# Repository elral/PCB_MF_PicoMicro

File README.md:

# ✈️ PicoMicro - ProMicro-Compatible Board from Mobiflight

This board is designed as a **drop-in replacement** for the classic Arduino Pro Micro (ATmega32U4), but powered by the **modern Raspberry Pi RP2350A microcontroller**.  
It keeps the same **form factor and pinout** while offering massive improvements in performance, memory, and connectivity — making it the **ideal choice for Mobiflight cockpits**.

---

## 🚀 Why PicoMicro for Mobiflight?

### ⚡ Drop-In Upgrade
- Identical footprint & pinout to the Arduino Pro Micro  
- Works with existing wiring and PCB layouts → **no hardware redesign required**  

### 📈 Higher Performance for Complex Cockpits
- **Dual-core ARM Cortex-M33 @ up to 150 MHz** (with FPU & DSP)  
- Handles many encoders, switches, LEDs, and displays simultaneously  
- **512 KB SRAM + up to 16 MB Flash** → no memory limits for complex setups  

### 🔌 Richer Connectivity
- **Native USB 2.0 FS/HS**  

### ⚡ True 5V Compatibility
- **5V-tolerant I/O pins** → safe with legacy 5V sensors, LEDs, and modules  
- Fully compatible with most cockpit electronics  

### 🔋 Efficiency & Reliability
- ARM-based low-power modes for large setups  
- Stable & future-proof, backed by Raspberry Pi Foundation support

---

## ⚠️ Known Limitations vs. Arduino Pro Micro

While this board is highly compatible, there are a few important differences:

1. **Analog Inputs**  
   - Only **A0 to A3** are available (4 total)  
   - Other analog pins present on the Pro Micro are not supported  

2. **5V Output (Pin 21)**  
   - On the Arduino Pro Micro, Pin 21 outputs **5V**  
   - On this board, Pin 21 outputs **3.3V**  

3. **MAX7219 & 5V Requirement**  
   - The MAX7219 driver must still be powered with **5V**  
   - Therefore, an **external 5V source** is required, or you can use **Pin 24 (Vin)**, which provides 5V directly from the USB connector  

4. **Level Shifting for MAX7219**  
   - The MAX7219 requires **5V logic levels**  
   - Use a **level shifter** between the PicoMicro board (3.3V signals) and the MAX7219 inputs  

5. **Bootloader Button**  
   - The board includes a **dedicated BOOT button** to enter USB mass storage boot mode (for firmware flashing).  

---

## 📊 PicoMicro vs. Arduino Pro Micro (ATmega32U4)

| Feature  | PicoMicro ProMicro                          | Arduino Pro Micro (ATmega32U4) |
|----------|-------------------------------------------|--------------------------------|
| MCU      | Dual-core ARM Cortex-M33 @ up to 150 MHz, FPU, DSP | 8-bit AVR @ 16 MHz |
| Flash    | Up to 16 MB QSPI (typ. 2–8 MB onboard)    | 32 KB |
| RAM      | 512 KB                                    | 2.5 KB |
| USB      | Native USB 2.0 FS/HS, multiple device classes | Native USB 2.0 FS (limited) |
| I/O      | **3.3 V logic, 5 V-tolerant pins**        | 5 V I/O (native) |
| Analog   | 4 (A0–A3 only)                            | 12 (depending on variant) |
| Extra HW | 2× PIO, Crypto engine, more UART/SPI/I²C | – |
| Power    | Low-power modes, efficient ARM design     | Limited power saving |

---

## 🔧 Example Wiring (MAX7219 with External 5V)

When using a MAX7219 with this PicoMicro board, note the following:

- The MAX7219 **requires 5V power** for reliable operation.
- The PicoMicro board only provides **3.3V logic**, so a **level shifter** is required on the SPI signals.
- Use the `Vin` pin (Pin 24, USB 5V) as the 5V source if no external supply is available.
- Do **not** use Pin 21 (`5V`), as it only provides 3.3V on this board.

#### Wiring Notes

- **Vin (5V USB)** → **VCC (5V MAX7219)**
- **GND** → **GND**
- **MOSI (3.3V)** → (via level shifter) → **DIN (5V)**
- **SCK (3.3V)** → (via level shifter) → **CLK (5V)**
- **CS (3.3V)** → (via level shifter) → **LOAD/CS (5V)**

Make sure to add a **3.3V → 5V level shifter** on the SPI signals to the MAX7219.

#### Block Diagram

---

## 🖥 Advantages for Mobiflight Community Devices

Many Mobiflight **Custom Devices** (Community Devices) are more complex and require more memory and processing power than the classic Arduino Pro Micro can provide.  
This board with the **RP2350A** offers clear advantages:

- **More Flash** → room for larger device code and libraries.  
- **More RAM** → essential for OLED displays and complex buffers.  
- **Higher performance** → smoother updates and faster response.  
- **Dual-Core CPU** → allows splitting tasks (e.g., handling displays and inputs in parallel).  
- **PIO offload** → precise timing for LEDs, drivers, or custom protocols  

This makes the PicoMicro board especially well-suited for **community-driven Mobiflight devices**, including setups with **OLED displays** and other resource-demanding modules.

---

## ✈️ Why It Matters for Mobiflight
- **Supports more devices per board** → fewer boards, fewer USB connections
- **Fast response times** → smoother input/output handling with no lag
- **Drop-in compatibility** → works in place of the Pro Micro in your cockpit modules  
- **Future-ready** → while the ATmega32U4 reaches its limits, the PicoMicro provides plenty of headroom for upcoming Mobiflight features  

---

## 📌 Summary
The **PicoMicro** is a **next-generation upgrade** built for Mobiflight cockpit builders:  
✅ More performance & memory  
✅ 5V-tolerant IO  
✅ 100% ProMicro form factor  
✅ Ideal for complex community devices, including OLEDs

> **Upgrade your cockpit today — with transparent compatibility notes for a smooth migration.**

## Additional information

### Bottom View

### Schematic

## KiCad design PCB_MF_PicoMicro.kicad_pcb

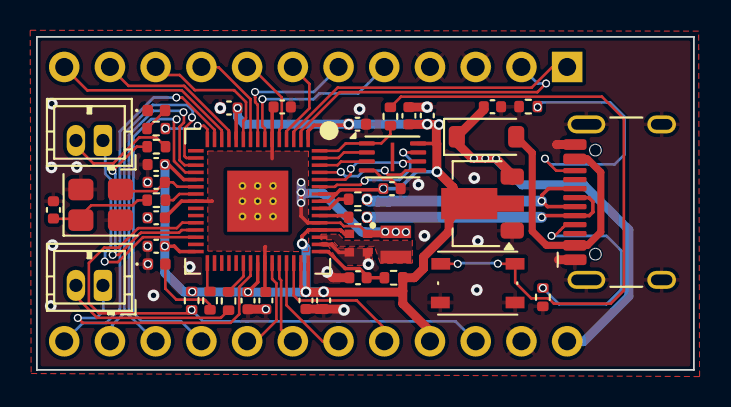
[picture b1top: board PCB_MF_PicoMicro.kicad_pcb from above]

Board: 2 copper layers, 36.5 x 18.5 mm, 44 parts (0 on the bottom side), 52 nets.

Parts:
C1, C2: 10uF; C_0402_1005Metric
C3: 100n; C_0402_1005Metric
C4, C5: 10pF; C_0402_1005Metric
C6, C7, C8, C9, C10, C11, C12, C13, C14, C15: 100nF; C_0402_1005Metric
C16, C17: 4.7u; C_0402_1005Metric_small_pads
C18: 4.7u; C_0402_1005Metric
C19: 4.7uF; C_0402_1005Metric
D1: D_Schottky; D_SOD-123
D2, D3: green; LED_0402_1005Metric
J1: PicoMicro
J3: USB_C_Receptacle_USB2.0_16P; USB_C_Receptacle_HCTL_HC-TYPE-C-16P-01A
J7, J8: Conn_01x02_Pin; JST_ZH_B2B-ZR_1x02_P1.50mm_Vertical
L1: 3.3u; L_pol_2016
R1, R2: 1k; R_0402_1005Metric
R3, R4: 27; R_0402_1005Metric
R5: 33; R_0402_1005Metric
R6: 10k; R_0402_1005Metric
R7, R8: 5.1k; R_0402_1005Metric
R9, R10: 200; R_0402_1005Metric
R11, R12: 50; R_0402_1005Metric
SW1: SW_Push; SW_Push_1P1T_NO_Vertical_Wuerth_434133025816
U1: RP2350A; RP2350A_QFN-60_EP_7.75x7.75_Pitch0.4mm
U2: AMS1117-3.3; SOT-89-3
U4: W25Q16JVSS; Winbond_USON-8-1EP_3x2mm_P0.5mm_EP0.2x1.6mm
Y1: X322512MSB4SI; Crystal_SMD_3225-4Pin_3.2x2.5mm

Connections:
3.3V: C2.1, C3.1, C9.1, C10.1, C11.1, C12.1, C13.1, C14.1, C15.1, C16.1, C19.1, J1.21 (+3.3V), R5.1, R6.1, U1.1 (IOVDD), U1.11 (IOVDD), U1.20 (IOVDD), U1.30 (IOVDD), U1.38 (IOVDD), U1.44 (ADC_AVDD), U1.45 (IOVDD), U1.49 (VREG_VIN), U1.53 (USB_OTP_VDD), U1.54 (QSPI_IOVDD), U2.2 (VO), U4.8 (VCC)
+1V1: C6.1, C7.1, C8.1, C17.1, L1.1, U1.6 (DVDD), U1.23 (DVDD), U1.39 (DVDD), U1.50 (VREG_FB)
/RP2350A/GPIO11: R9.2, U1.15 (GPIO11)
/RP2350A/GPIO19: R10.2, U1.31 (GPIO19)
/RP2350A/QSPI_SCLK: U1.56 (QSPI_SCLK), U4.6 (CLK)
/RP2350A/QSPI_SD0: U1.57 (QSPI_SD0), U4.5 (DI(IO0))
/RP2350A/QSPI_SD1: U1.59 (QSPI_SD1), U4.2 (DO(IO1))
/RP2350A/QSPI_SD2: U1.58 (QSPI_SD2), U4.3 (IO2)
/RP2350A/QSPI_SD3: U1.55 (QSPI_SD3), U4.7 (IO3)
/RP2350A/QSPI_SS: R1.1, U1.60 (QSPI_SS), U4.1 (~CS)
/RP2350A/RAW: D1.2 (A), J3.A4 (VBUS), J3.A9 (VBUS), J3.B4 (VBUS), J3.B9 (VBUS)
/RP2350A/USB_D+: J3.A6 (D+), J3.B6 (D+), R3.1
/RP2350A/USB_D-: J3.A7 (D-), J3.B7 (D-), R4.1
/RP2350A/USB_D_R+: R3.2, U1.52 (USB_DP)
/RP2350A/USB_D_R-: R4.2, U1.51 (USB_DM)
/RP2350A/VREG_LX: L1.2, U1.48 (VREG_LX)
/RP2350A/XIN: C4.1, U1.21 (XIN), Y1.3
/RP2350A/XOUT_R: R2.1, U1.22 (XOUT)
/RP2350A/~USB_BOOT: R1.2, SW1.2
A0: J1.17 (18(A0)), U1.40 (GPIO26_ADC0)
A1: J1.18 (19(A1)), U1.41 (GPIO27_ADC1)
A2: J1.19 (20(A2)), U1.42 (GPIO28_ADC2)
A3: J1.20 (21(A3)), U1.43 (GPIO29_ADC3)
D0: J1.2 (0(PWM)/RX), U1.2 (GPIO0)
D1: J1.1 (1(PWM)/TX), U1.3 (GPIO1)
D2: J1.7 (4(PWM)), U1.4 (GPIO2)
D3: J1.8 (5(PWM)), U1.5 (GPIO3)
D4: J1.5 (2(PWM)/SDA), U1.7 (GPIO4)
D5: J1.6 (3(PWM)/SCL), U1.8 (GPIO5)
D6: J1.9 (6(PWM)), U1.9 (GPIO6)
D7: J1.10 (7(PWM)), U1.10 (GPIO7)
D8: J1.11 (8(PWM)), U1.12 (GPIO8)
D9: J1.12 (9(PWM)), U1.13 (GPIO9)
D10: J1.13 (10(PWM)), U1.14 (GPIO10)
D13: J1.14 (16), U1.17 (GPIO13)
D14: J1.15 (14), U1.18 (GPIO14)
D15: J1.16 (15), U1.19 (GPIO15)
GND: C1.2, C2.2, C3.2, C4.2, C5.2, C6.2, C7.2, C8.2, C9.2, C10.2, C11.2, C12.2, C13.2, C14.2, C15.2, C16.2, C17.2, C18.2, C19.2, D2.1 (K), D3.1 (K), J1.3 (GND), J1.4 (GND), J1.23 (GND), J3.A1 (GND), J3.A12 (GND), J3.B1 (GND), J3.B12 (GND), J3.S1 (SHIELD), R7.1, R8.1, SW1.1, U1.47 (VREG_PGND), U1.61 (GND), U2.1 (GND), U4.4 (GND), Y1.2, Y1.4
unnamed: C5.1, R2.2, Y1.1
unnamed: D2.2 (A), R10.1
unnamed: D3.2 (A), R9.1
unnamed: J3.A5 (CC1), R7.2
unnamed: J3.B5 (CC2), R8.2
unnamed: J7.2, R11.1
unnamed: J8.2, R12.1
unnamed: C18.1, R5.2, U1.46 (VREG_AVDD)
RST: J1.22 (RESET), R6.2, U1.26 (RUN)
RX1: J7.1, U1.28 (GPIO17)
RX2: J8.1, U1.37 (GPIO25)
TX1: R11.2, U1.27 (GPIO16)
TX2: R12.2, U1.36 (GPIO24)
VIN: C1.1, D1.1 (K), J1.24 (VIN), U2.3 (VI)

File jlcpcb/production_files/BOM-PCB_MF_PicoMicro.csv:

Comment,Designator,Footprint,LCSC,Quantity
1k,"R1,R2",R_0402_1005Metric,C11702,2
100nF,"C10,C11,C12,C13,C14,C15,C3,C6,C7,C8,C9",C_0402_1005Metric,C1525,11
10uF,"C1,C2",C_0402_1005Metric,C15525,2
4.7u,"C16,C17,C18,C19",C_0402_1005Metric_small_pads,C23733,4
200,"R10,R9",R_0402_1005Metric,C25087,2
27,"R3,R4",R_0402_1005Metric,C25100,2
33,R5,R_0402_1005Metric,C25105,1
50,"R11,R12",R_0402_1005Metric,C25120,2
10k,R6,R_0402_1005Metric,C25744,1
5.1k,"R7,R8",R_0402_1005Metric,C25905,2
W25Q16JVSS,U4,Winbond_USON-8-1EP_3x2mm_P0.5mm_EP0.2x1.6mm,C2843335,1
Conn_01x02_Pin,"J7,J8",JST_ZH_B2B-ZR_1x02_P1.50mm_Vertical,C2845550,2
USB_C_Receptacle_USB2.0_16P,J3,USB_C_Receptacle_HCTL_HC-TYPE-C-16P-01A,C2997432,1
10pF,"C4,C5",C_0402_1005Metric,C32949,2
AMS1117-3.3,U2,SOT-89-3,C347256,1
green,"D2,D3",LED_0402_1005Metric,C401111,2
RP2350A,U1,RP2350A_QFN-60_EP_7.75x7.75_Pitch0.4mm,C42411118,1
3.3u,L1,L_pol_2016,C42411119,1
D_Schottky,D1,D_SOD-123,C5377901,1
X322512MSB4SI,Y1,Crystal_SMD_3225-4Pin_3.2x2.5mm,C9002,1
SW_Push,SW1,SW_Push_1P1T_NO_Vertical_Wuerth_434133025816,C92589,1
Conn_01x12,J2,PinHeader_1x12_P2.54mm_Vertical,,1
Conn_01x12,J1,PinHeader_1x12_P2.54mm_Vertical,,1

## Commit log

2025-08-09 first upload
2025-08-09 first changes for RP2350A
2025-08-10 power supply lines routed
2025-08-11 fixed all warnings/errors
2025-08-11 add parts for 1.1V regulator
2025-08-12 optimazations
2025-08-12 add LED, make board smaller
2025-08-14 add 2nd LED
2025-08-14 add missing R for LEDs, add production files for JLCPCB
2025-08-14 minor layout optimazations, update production files
2025-08-14 update production files acc. order
2025-08-15 first version of Readme
2025-08-21 replace ProMicro against pin header connectors
2025-08-22 change ProMicro footprint to standard connector
2025-08-22 change ProMicro footprint to standard connector
    commit eacd6e6b7c88736312cbb7fe5e411177d7c22398
    Author: elral <3263285+elral@users.noreply.github.com>
    Date: Thu Aug 21 06:40:23 2025 +0200
    replace ProMicro against pin header connectors
2025-08-22 add cap for AVDD, fix wrong cap value 1V1
2025-08-23 better formatting
2025-08-23 fixed wrong link to png file
2025-08-23 pictures added, some more updates
2025-08-23 add schematic, new chapter for additional informatio
2025-08-23 w/o badges
2025-08-24 add topic in chapter advantages
2025-08-24 fixed wrong naming for pictures
2025-08-27 better routing of USB_BOOT track
2025-09-01 serial resistor for TX line
2025-09-01 route both additional resistors
2025-09-01 update production files
2025-09-02 swap tx line to slave, better arrangement of parts
2025-09-04 better positioning of parts
2025-09-04 Swap TX/RX line from connection to slave
    * swap tx line to slave, better arrangement of parts
    * better positioning of parts
2025-09-10 add SDA and SCL markings
2025-09-21 use new PicoMicro Symbol and footprint
2025-09-25 PicoMicro footprint updated
